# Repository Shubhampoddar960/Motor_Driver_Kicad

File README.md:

1. \# 🚗⚡ L298N Motor Driver (KiCad)

# 

# A motor driver board designed in \*\*KiCad\*\* around the \*\*L298N dual H-bridge\*\* driver. Use it to control the speed and direction of DC motors from a microcontroller such as an ESP32 or Arduino. 🤖

# 

# \---

# 

# \## 📸 Screenshots

# 

# Screenshots of the schematic, PCB layout and 3D view are in the \[`screenshots`](screenshots/) folder.

# 

# \---

# 

# \## ✨ Features

# 

# \- 🔄 Dual H-bridge: drive \*\*two DC motors\*\* independently

# \- ↔️ Forward / reverse control for each motor

# \- 🎚️ Speed control using PWM on the enable pins

# \- 🔌 Screw terminals or headers for power and motor outputs

# \- 🧠 Logic-level inputs for a microcontroller

# 

# > ✏️ Edit this list to match what your board actually includes.

# 

# \---

# 

# \## 📁 Repository Structure

# 

# ```

# Motor\_Driver\_Kicad/

# ├── L298N\_design/

# │   ├── L298N\_design.kicad\_pro   🗂️ KiCad project file

# │   ├── L298N\_design.kicad\_sch   📐 Schematic

# │   └── L298N\_design.kicad\_pcb   🟩 PCB layout

# ├── screenshots/                 🖼️ Images of the design

# ├── .gitignore

# └── README.md

# ```

# 

# \---

# 

# \## 🛠️ Tools Used

# 

# | Tool | Purpose |

# |------|---------|

# | 🧰 KiCad | Schematic capture and PCB design |

# | 🌱 Git \& GitHub | Version control |

# 

# \---

# 

# \## 🚀 How to Open the Project

# 

# 1\. 📥 Clone the repository:

# &#x20;  ```bash

# &#x20;  git clone https://github.com/Shubhampoddar960/Motor\_Driver\_Kicad.git

# &#x20;  ```

# 2\. 📂 Open KiCad and choose \*\*File → Open Project\*\*.

# 3\. 🗂️ Select `L298N\_design/L298N\_design.kicad\_pro`.

# 4\. 👀 Open the schematic or PCB editor from the project window.

# 

# \---

# 

# \## 🔌 Pin Connections

# 

# | Signal | Description |

# |--------|-------------|

# | `IN1`, `IN2` | 🔁 Direction control for Motor A |

# | `IN3`, `IN4` | 🔁 Direction control for Motor B |

# | `ENA`, `ENB` | 🎚️ PWM speed control for Motors A and B |

# | `VS` | 🔋 Motor supply voltage |

# | `GND` | ⏚ Common ground |

# | `OUT1`–`OUT4` | ⚙️ Motor outputs |

# 

# > ✏️ Adjust the names to match the labels in your schematic.

# 

# \---

# 

# \## ⚠️ Notes

# 

# \- 🔥 The L298N drops about 2 V per bridge and can get hot, so add a heatsink for higher currents.

# \- 🔗 Always connect the microcontroller ground to the driver ground.

# \- 🧪 Check the design carefully before ordering or manufacturing a PCB.

# 

# \---

# 

# \## 🗺️ Future Improvements

# 

# \- \[ ] 🧩 Add a 3D model preview

# \- \[ ] 📦 Export Gerber files

# \- \[ ] 💡 Add status LEDs

# \- \[ ] 🛡️ Add protection circuitry

# 

# \---

# 

# \## 👤 Author

# 

# \*\*Shubham Poddar\*\*

# 🔗 GitHub: \[@Shubhampoddar960](https://github.com/Shubhampoddar960)

# 

# \---

# 

# \## 📄 License

# 

# No license has been added yet. 📝 Add one if you want others to reuse or modify the design.

# 

# \---

# 

# ⭐ If you find this project useful, consider giving it a star!

#-----------------------------------------------------------------------------------------------------------------------------------------------------------------|
#-----------------------------------------------------------------------------------------------------------------------------------------------------------------|

2. ⚙️ TB6612FNG Motor Driver Board

A compact dual DC motor driver board designed in **KiCad**, built around the **TB6612FNG** driver IC. It includes reverse polarity protection and proper supply filtering, which makes it a good fit for robotics projects such as line followers and small robots. 🤖

---

## ✨ Features

- 🔌 Drives **2 DC motors** independently (Channel A and Channel B)
- 🛡️ **Reverse polarity protection** using a PMOS (Q1)
- 🔋 Motor supply filtering (10 µF + 0.1 µF)
- 🧠 Logic supply decoupling (0.1 µF)
- 🌍 Large **GND copper pour** for good return paths and noise reduction
- 📌 Simple headers: one for signals, one for power and motors
- 🔄 Standby (STBY) pin to put the driver to sleep and save power

---

## 🧩 Specifications (TB6612FNG)

| Parameter | Value |
|---|---|
| ⚡ Motor supply (VMOT) | 4.5 V – 13.5 V |
| 🧠 Logic supply (VCC) | 2.7 V – 5.5 V |
| 🔁 Continuous current per channel | 1.2 A (3.2 A peak) |
| 🎚️ PWM frequency | Up to 100 kHz |

---

## 📌 Pinout

### 🔹 J1 – Signal Header (7 pins)

| Pin | Signal | Description |
|---|---|---|
| 1 | AIN1 | Motor A direction input 1 |
| 2 | AIN2 | Motor A direction input 2 |
| 3 | PWMA | Motor A speed (PWM) |
| 4 | BIN1 | Motor B direction input 1 |
| 5 | BIN2 | Motor B direction input 2 |
| 6 | PWMB | Motor B speed (PWM) |
| 7 | STBY | Standby (HIGH = enabled) |

### 🔹 J2 – Power & Motor Header (7 pins)

| Pin | Signal | Description |
|---|---|---|
| 1 | VMOT | Battery / motor

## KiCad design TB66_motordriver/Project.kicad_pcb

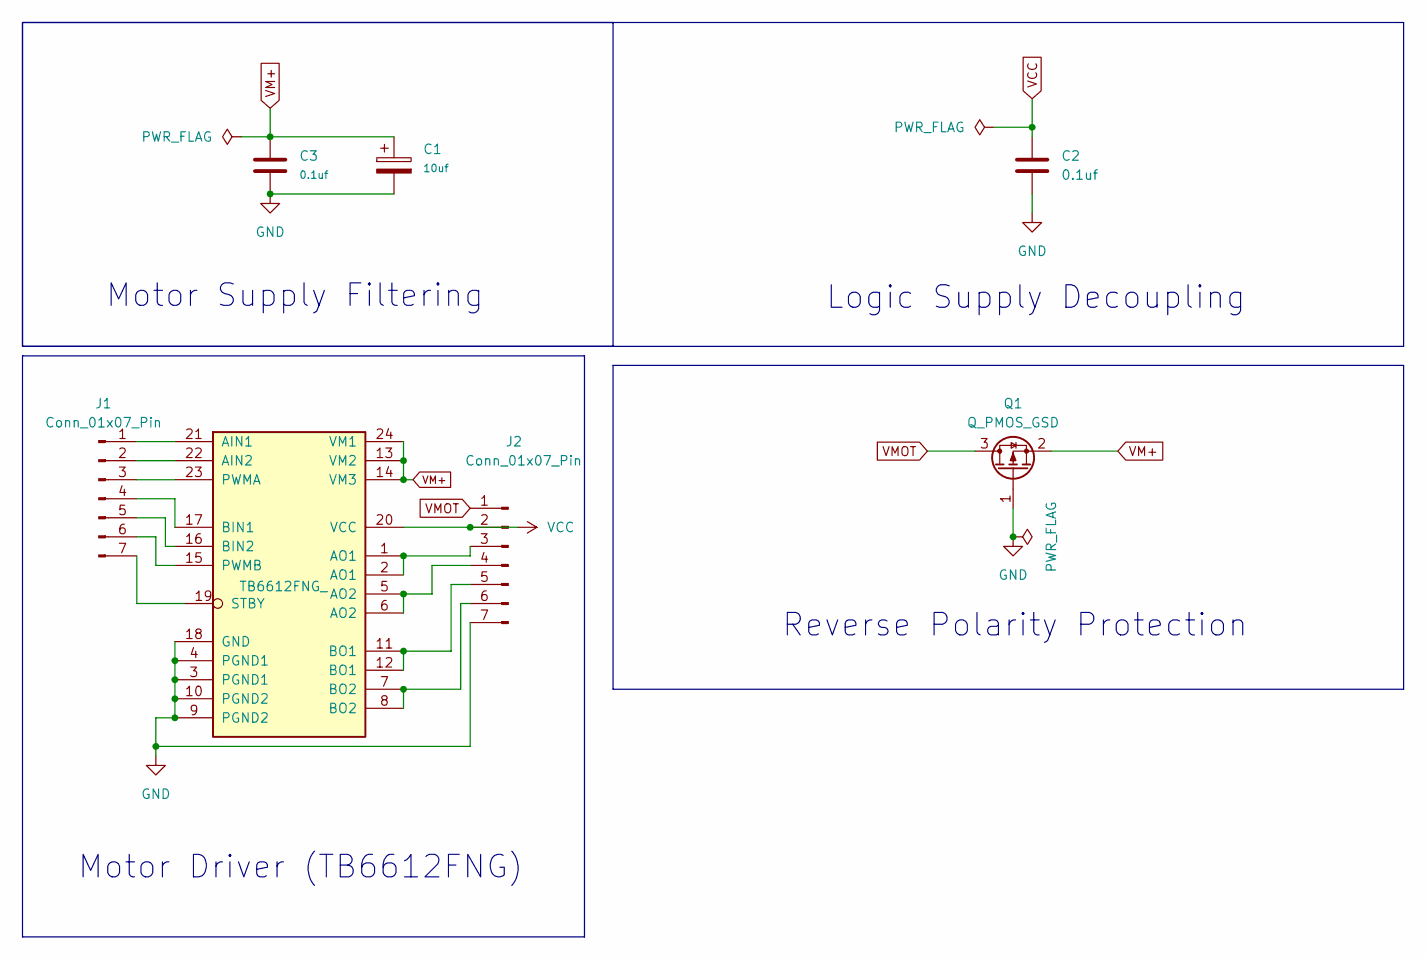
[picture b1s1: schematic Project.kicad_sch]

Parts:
C1: 10uf; CP_Elec_5x5.4
C2, C3: 0.1uf; C_0603_1608Metric
J1, J2: Conn_01x07_Pin; PinHeader_1x07_P2.54mm_Vertical
Q1: Q_PMOS_GSD; SOT-23
U1: TB6612FNG_; SSOP-24_5.3x8.2mm_P0.65mm

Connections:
GND: C1.2, C2.2, C3.2, J2.7, Q1.1 (G), U1.3 (PGND1), U1.4 (PGND1), U1.9 (PGND2), U1.10 (PGND2), U1.18 (GND)
unnamed: J1.1, U1.21 (AIN1)
unnamed: J1.2, U1.22 (AIN2)
unnamed: J1.3, U1.23 (PWMA)
unnamed: J1.4, U1.17 (BIN1)
unnamed: J1.5, U1.16 (BIN2)
unnamed: J1.6, U1.15 (PWMB)
unnamed: J1.7, U1.19 (STBY)
unnamed: J2.3, U1.1 (AO1), U1.2 (AO1)
unnamed: J2.4, U1.5 (AO2), U1.6 (AO2)
unnamed: J2.5, U1.11 (BO1), U1.12 (BO1)
unnamed: J2.6, U1.7 (BO2), U1.8 (BO2)
VCC: C2.1, J2.2, U1.20 (VCC)
VM+: C1.1, C3.1, Q1.2 (S), U1.13 (VM2), U1.14 (VM3), U1.24 (VM1)
VMOT: J2.1, Q1.3 (D)

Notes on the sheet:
Reverse Polarity Protection
Motor Driver (TB6612FNG)
Motor Supply Filtering
Logic Supply Decoupling

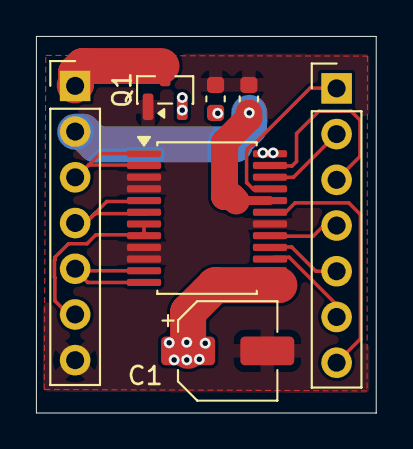
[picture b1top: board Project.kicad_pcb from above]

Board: 4 copper layers, 18.9 x 20.9 mm, 7 parts (0 on the bottom side), 15 nets.

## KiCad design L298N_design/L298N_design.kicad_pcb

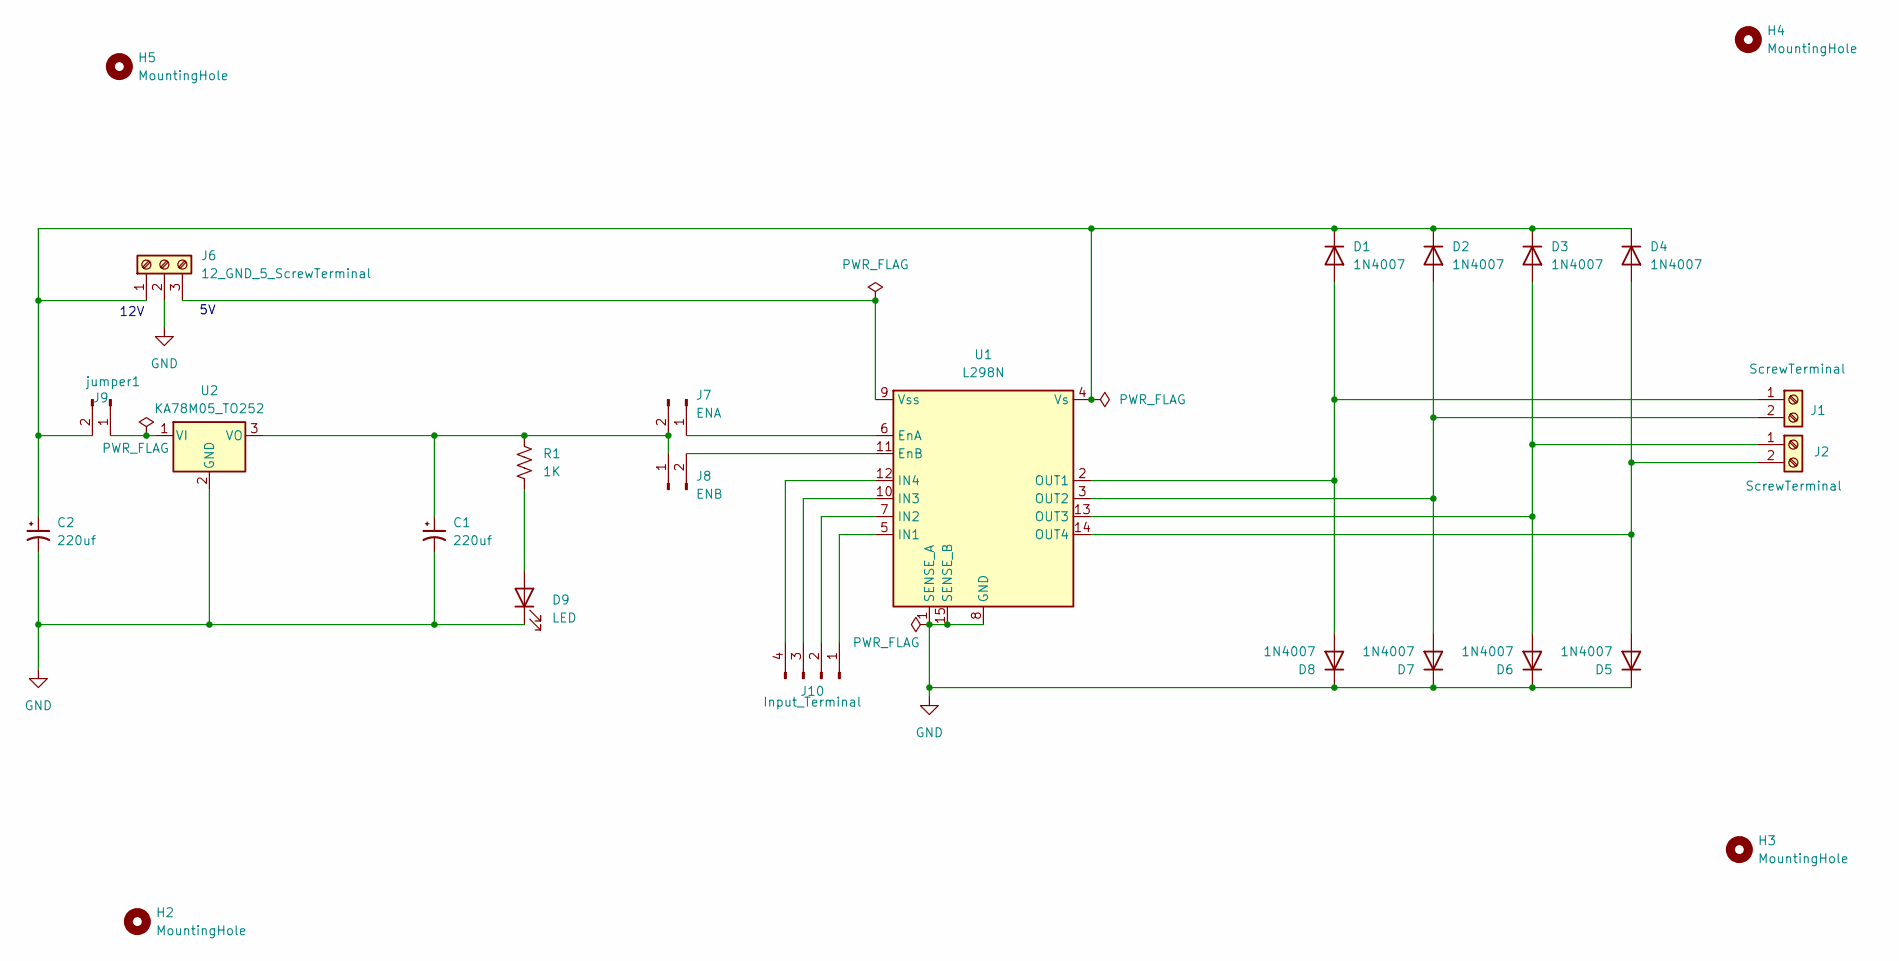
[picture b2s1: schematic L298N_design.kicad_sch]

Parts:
C1, C2: 220uf; CP_Radial_D8.0mm_P3.50mm
D1, D2, D3, D4, D5, D6, D7, D8: 1N4007; LED_0805_2012Metric
D9: LED; LED_0805_2012Metric
H2, H3, H4, H5: MountingHole; MountingHole_2.2mm_M2
J1, J2: ScrewTerminal; TerminalBlock_CUI_TB007-508-02_1x02_P5.08mm_Horizontal
J6: 12_GND_5_ScrewTerminal; TerminalBlock_CUI_TB007-508-03_1x03_P5.08mm_Horizontal
J7: ENA; PinHeader_1x02_P2.54mm_Vertical
J8: ENB; PinHeader_1x02_P2.54mm_Vertical
J9: jumper1; PinHeader_1x02_P2.54mm_Vertical
J10: Input_Terminal; PinHeader_1x04_P2.54mm_Vertical
R1: 1K; LED_0805_2012Metric
U1: L298N; TO-220-15_P2.54x5.08mm_StaggerEven_Lead4.58mm_Vertical
U2: KA78M05_TO252; TO-252-3_TabPin2

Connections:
GND: C1.2, C2.2, D5.1 (K), D6.1 (K), D7.1 (K), D8.1 (K), D9.1 (K), J6.2, U1.1 (SENSE_A), U1.8 (GND), U1.15 (SENSE_B), U2.2 (GND)
unnamed: D1.2 (A), D8.2 (A), J1.1, U1.2 (OUT1)
unnamed: C2.1, D1.1 (K), D2.1 (K), D3.1 (K), D4.1 (K), J6.1, J9.2, U1.4 (Vs)
unnamed: D2.2 (A), D7.2 (A), J1.2, U1.3 (OUT2)
unnamed: D3.2 (A), D6.2 (A), J2.1, U1.13 (OUT3)
unnamed: D4.2 (A), D5.2 (A), J2.2, U1.14 (OUT4)
unnamed: D9.2 (A), R1.2
unnamed: J6.3, U1.9 (Vss)
unnamed: J7.1, U1.6 (EnA)
unnamed: C1.1, J7.2, J8.1, R1.1, U2.3 (VO)
unnamed: J8.2, U1.11 (EnB)
unnamed: J9.1, U2.1 (VI)
unnamed: J10.1, U1.5 (IN1)
unnamed: J10.2, U1.7 (IN2)
unnamed: J10.3, U1.10 (IN3)
unnamed: J10.4, U1.12 (IN4)

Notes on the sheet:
12V

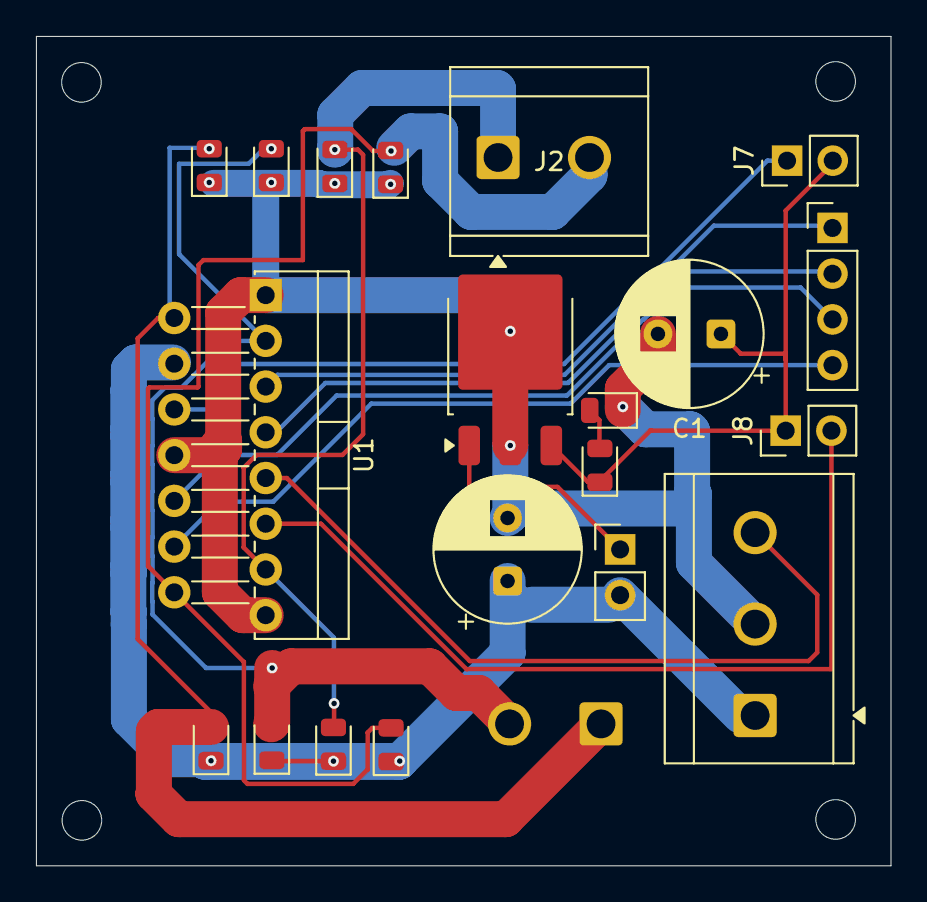
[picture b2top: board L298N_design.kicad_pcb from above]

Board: 2 copper layers, 47.5 x 46.1 mm, 25 parts (1 on the bottom side), 16 nets.
